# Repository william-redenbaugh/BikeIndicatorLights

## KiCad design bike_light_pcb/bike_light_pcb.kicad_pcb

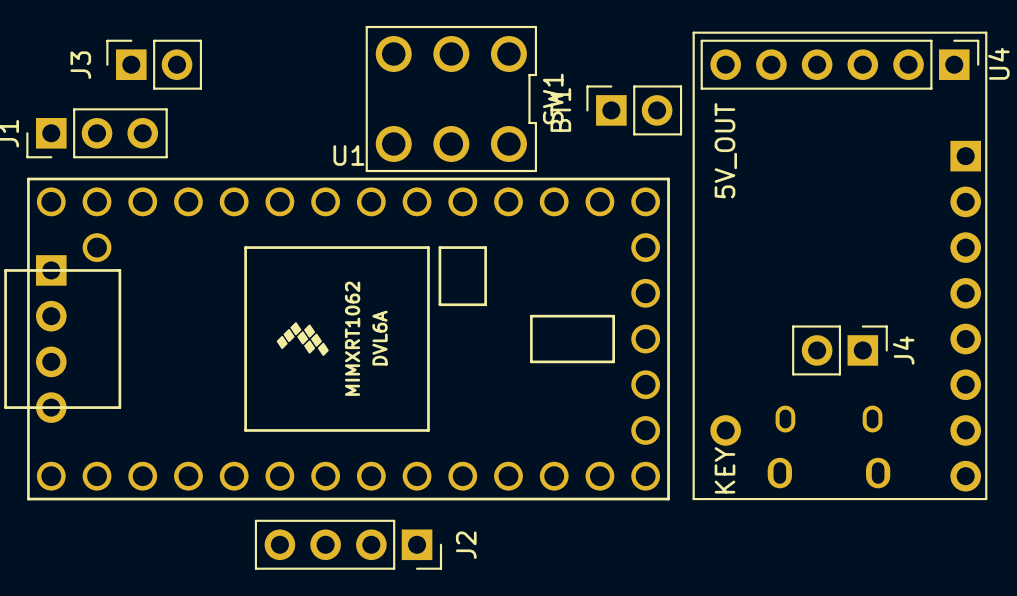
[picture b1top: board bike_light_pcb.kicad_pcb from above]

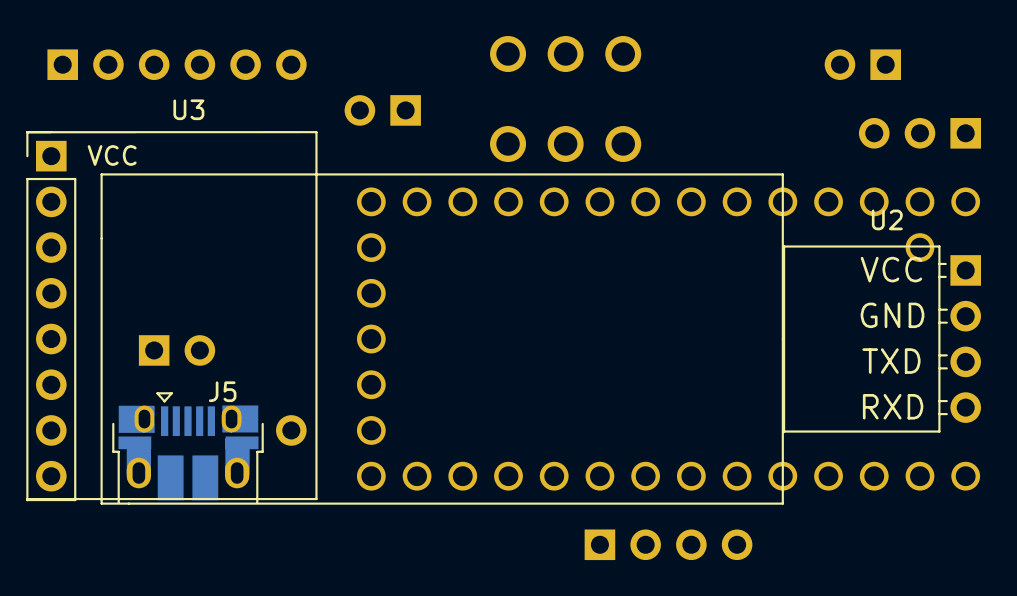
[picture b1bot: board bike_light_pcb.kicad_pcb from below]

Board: 2 copper layers, 11 parts (3 on the bottom side), 20 nets, no tracks yet.

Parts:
BT1: Battery_Cell; PinSocket_1x02_P2.54mm_Vertical
J1: Conn_01x03_Male; PinHeader_1x03_P2.54mm_Vertical
J2: Conn_01x04_Female; PinSocket_1x04_P2.54mm_Vertical
J3: Conn_01x02_Female; PinSocket_1x02_P2.54mm_Vertical
J4: Conn_01x02_Female; PinHeader_1x02_P2.54mm_Vertical
J5: USB_B_Micro_Charge; USB_Micro-B_Amphenol_10103594-0001LF_Horizontal
SW1: SW_Push_DPDT; SLIDE_SW_OS202013MT8QN1
U1: Teensy4.0; Teensy40
U2: HM18_BLE
U3: MPU605; MPU6050_module
U4: charge_module

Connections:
5V_CHRG: J4.1, J5.1, U4.1
5V_MAIN: J1.1, J3.1, SW1.2, U2.1, U3.1
5V_MODULE: SW1.1, U4.6
CHRG_KEY: U1.11, U4.7
GND_CHRG: J4.2, J5.5, U4.2
GND_MAIN: J1.3, J3.2, SW1.5, U1.17, U1.32, U2.2, U3.2
GND_MODULE: SW1.4, U4.5
unnamed: BT1.1, U4.4
unnamed: BT1.2, U4.3
unnamed: J2.1, U1.10
unnamed: J2.2, U1.9
unnamed: J2.3, U1.7
unnamed: J2.4, U1.6
unnamed: U1.2, U2.4
unnamed: U1.3, U2.3
unnamed: U1.22, U3.8
unnamed: U1.25, U3.4
unnamed: U1.26, U3.3
RGB_D: J1.2, U1.27
TEENSY_VUSB: SW1.3, U1.34

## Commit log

2020-09-02 started development on LED Matrix drivers
2020-09-02 simplifying
2020-09-02 added LED driver code for APA102s
2020-09-02 added documentation for apa102 LEDs
2020-09-03 okay back to square one...
2020-09-04 started refractoring code for personal use
2020-09-04 forgot to make sure gammaLUT is there...
2020-09-04 more hub75 refractoring
2020-09-05 stuff
2020-09-05 started testing with light animation engine layer
2020-09-06 imported imu module and continued to add more basic animations to build core functionality
2020-09-06 refractoed the matrix code to make more sense
2020-09-06 switched mpu modules for more signal filtering and data conversiosn
2020-09-07 switched back to fork of previous library
2020-09-07 updated subrepos
2020-09-07 started own imu module, added documentation
2020-09-07 added more documentation, enumerated setup status, more implementation details
2020-09-07 completed implentation of imu, but system is still untested
2020-09-08 completed testing of imu, added conversion features, started development of matrix engine
2020-09-09 started working on bluetooth module
2020-09-10 started android dev
2020-09-10 updated subrepos and got bluetooth over uart setup with protocallbacks
2020-09-10 updated App layout
2020-09-11 added some comments to make life easier
2020-09-12 cleaned up something
2020-09-14 refractored a bunch of stufF
2020-09-15 completed LED signaling with will-os
2020-09-15 changed animations to something more inline with a vehicle
2020-09-15 started testing runtimes
2020-09-21 changed how sleep mode is implemented so we don't waste time context switching with not necesary
2020-09-22 started dev on battery module
2020-09-23 updated subrepos on semaphores
2020-09-25 added subrepos
2020-09-27 moved some stuff into repos, updated subrepos
2020-10-01 updated submodules
2020-10-01 added ringbuffer
2020-10-03 start symbols and footprints
2020-10-03 created mpu6050 footprint
2020-10-05 start schematic
2020-10-06 draft 1 schem
2020-10-06 draft of general layout
2020-11-15 fixing changes for revised kernel
2020-11-15 bug fix analyzation
2020-11-27 working on refractoring the scheduler
2020-11-27 validated base braking functionality, tuned software
2020-11-27 more fine tuning
2020-11-29 Update imu_runtime.cpp
    Fixed adjustements for imu runtime
2020-11-29 Update led_strip_runtime.cpp
    updated animations for LED strip runtime code.
